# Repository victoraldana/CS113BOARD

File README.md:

# CS113BOARD – Placa de Control

Placa de control diseñada en **KiCad** para el proyecto de *Laboratorio de Electrónica 3* (Universidad, 2026). Usa un módulo **ESP32-S3-DevKitC** como controlador, con una etapa de *latches* (74LS75), un decodificador (74LS138) y *drivers* de potencia (ULN2803A) que se conectan a la carga por conectores JST.

## Contenido del repositorio

| Archivo | Descripción |
|---|---|
| `PLACA DE CONTROL.kicad_pro` | Archivo de proyecto de KiCad |
| `PLACA DE CONTROL.kicad_sch` | Esquemático |
| `PLACA DE CONTROL.kicad_pcb` | Diseño del PCB (espesor 1.6 mm) |
| `PLACA DE CONTROL.kicad_prl` | Preferencias locales del proyecto |
| `PLACA DE CONTROL.png` | Render 3D de la placa |
| `la.pdf` | Documentación de apoyo |
| `LICENSE` | Licencia del proyecto |

## Componentes principales

| Cantidad | Componente | Encapsulado | Función |
|:-:|---|---|---|
| 1 | ESP32-S3-DevKitC | 2 × `PinSocket_1x22_P2.54mm` | Microcontrolador |
| 1 | 74LS138 | DIP-16 | Decodificador 3 a 8 |
| 6 | 74LS75 | DIP-16 | Latches de 4 bits |
| 6 | ULN2803A | DIP-18 | Driver de 8 canales (Darlington) |
| 6 | Conector 1×06 | JST XH B6B-XH-A (2.50 mm) | Conexión a la carga |
| 1 | Conector 1×04 | JST EH B4B-EH-A (2.50 mm) | Conexión auxiliar |

Alimentación: **+5 V** (lógica) y **+12 V** (etapa de potencia), con **GND** común.

## Cómo abrir el proyecto

1. Instala [KiCad](https://www.kicad.org/download/). El proyecto usa el formato de la versión 8 o superior.
2. Clona el repositorio:
   ```bash
   git clone https://github.com/victoraldana/CS113BOARD.git
   ```
3. Abre `PLACA DE CONTROL.kicad_pro`.

## Fabricación

Desde el editor de PCB de KiCad:

1. `Archivo → Fabricación → Archivos Gerber` y `Archivos de taladrado`.
2. Comprueba las reglas con `Inspeccionar → Comprobador de reglas de diseño (DRC)`.
3. Envía los archivos generados al fabricante.

## Licencia

Distribuido bajo la licencia incluida en [LICENSE](LICENSE).

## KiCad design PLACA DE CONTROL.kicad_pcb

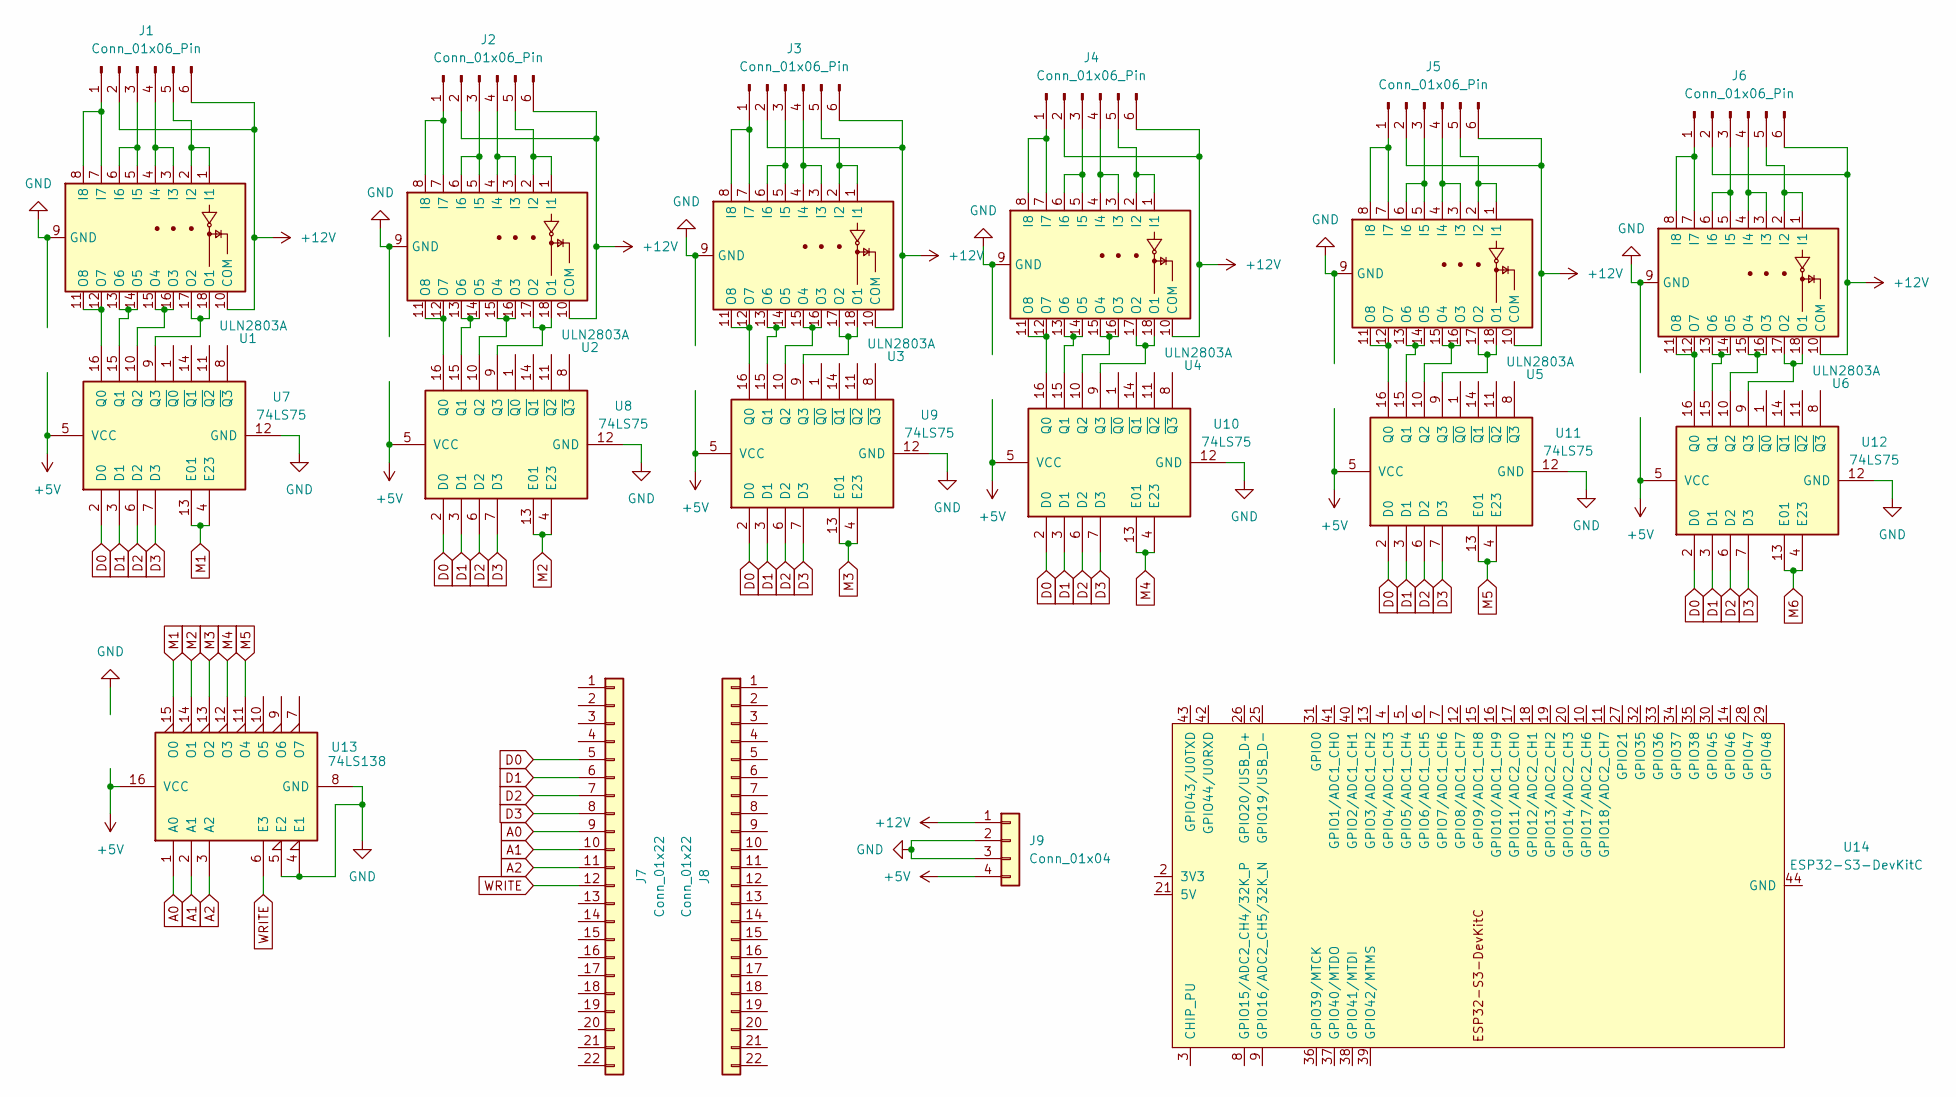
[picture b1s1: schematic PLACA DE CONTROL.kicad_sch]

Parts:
J1, J2, J3, J4, J5, J6: Conn_01x06_Pin; JST_XH_B6B-XH-A_1x06_P2.50mm_Vertical
J7, J8: Conn_01x22; PinSocket_1x22_P2.54mm_Vertical
J9: Conn_01x04; JST_EH_B4B-EH-A_1x04_P2.50mm_Vertical
U1, U2, U3, U4, U5, U6: ULN2803A; DIP-18_W7.62mm_LongPads
U7, U8, U9, U10, U11, U12: 74LS75; DIP-16_W7.62mm
U13: 74LS138; DIP-16_W7.62mm
U14: ESP32-S3-DevKitC

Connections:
+5V: J8.2, J9.4, U7.5 (VCC), U8.5 (VCC), U9.5 (VCC), U10.5 (VCC), U11.5 (VCC), U12.5 (VCC), U13.16 (VCC)
+12V: J1.2, J1.6, J2.2, J2.6, J3.2, J3.6, J4.2, J4.6, J5.2, J5.6, J6.2, J6.6, J9.1, U1.10 (COM), U2.10 (COM), U3.10 (COM), U4.10 (COM), U5.10 (COM), U6.10 (COM)
A0: J7.9, U13.1 (A0)
A1: J7.10, U13.2 (A1)
A2: J7.11, U13.3 (A2)
D0: J7.5, U7.2 (D0), U8.2 (D0), U9.2 (D0), U10.2 (D0), U11.2 (D0), U12.2 (D0)
D1: J7.6, U7.3 (D1), U8.3 (D1), U9.3 (D1), U10.3 (D1), U11.3 (D1), U12.3 (D1)
D2: J7.7, U7.6 (D2), U8.6 (D2), U9.6 (D2), U10.6 (D2), U11.6 (D2), U12.6 (D2)
D3: J7.8, U7.7 (D3), U8.7 (D3), U9.7 (D3), U10.7 (D3), U11.7 (D3), U12.7 (D3)
GND: J8.1, J9.2, J9.3, U1.9 (GND), U2.9 (GND), U3.9 (GND), U4.9 (GND), U5.9 (GND), U6.9 (GND), U7.12 (GND), U8.12 (GND), U9.12 (GND), U10.12 (GND), U11.12 (GND), U12.12 (GND), U13.4 (E1), U13.5 (E2), U13.8 (GND)
M1: U7.4 (E23), U7.13 (E01), U13.15 (O0)
M2: U8.4 (E23), U8.13 (E01), U13.14 (O1)
M3: U9.4 (E23), U9.13 (E01), U13.13 (O2)
M4: U10.4 (E23), U10.13 (E01), U13.12 (O3)
M5: U11.4 (E23), U11.13 (E01), U13.11 (O4)
M6: U12.4 (E23), U12.13 (E01), U13.10 (O5)
unnamed: J1.1, U1.7 (I7), U1.8 (I8)
unnamed: J1.3, U1.5 (I5), U1.6 (I6)
unnamed: J1.4, U1.3 (I3), U1.4 (I4)
unnamed: J1.5, U1.1 (I1), U1.2 (I2)
unnamed: J2.1, U2.7 (I7), U2.8 (I8)
unnamed: J2.3, U2.5 (I5), U2.6 (I6)
unnamed: J2.4, U2.3 (I3), U2.4 (I4)
unnamed: J2.5, U2.1 (I1), U2.2 (I2)
unnamed: J3.1, U3.7 (I7), U3.8 (I8)
unnamed: J3.3, U3.5 (I5), U3.6 (I6)
unnamed: J3.4, U3.3 (I3), U3.4 (I4)
unnamed: J3.5, U3.1 (I1), U3.2 (I2)
unnamed: J4.1, U4.7 (I7), U4.8 (I8)
unnamed: J4.3, U4.5 (I5), U4.6 (I6)
unnamed: J4.4, U4.3 (I3), U4.4 (I4)
unnamed: J4.5, U4.1 (I1), U4.2 (I2)
unnamed: J5.1, U5.7 (I7), U5.8 (I8)
unnamed: J5.3, U5.5 (I5), U5.6 (I6)
unnamed: J5.4, U5.3 (I3), U5.4 (I4)
unnamed: J5.5, U5.1 (I1), U5.2 (I2)
unnamed: J6.1, U6.7 (I7), U6.8 (I8)
unnamed: J6.3, U6.5 (I5), U6.6 (I6)
unnamed: J6.4, U6.3 (I3), U6.4 (I4)
unnamed: J6.5, U6.1 (I1), U6.2 (I2)
unnamed: U1.17 (O2), U1.18 (O1), U7.9 (Q3)
unnamed: U1.15 (O4), U1.16 (O3), U7.10 (Q2)
unnamed: U1.13 (O6), U1.14 (O5), U7.15 (Q1)
unnamed: U1.11 (O8), U1.12 (O7), U7.16 (Q0)
unnamed: U2.17 (O2), U2.18 (O1), U8.9 (Q3)
unnamed: U2.15 (O4), U2.16 (O3), U8.10 (Q2)
unnamed: U2.13 (O6), U2.14 (O5), U8.15 (Q1)
unnamed: U2.11 (O8), U2.12 (O7), U8.16 (Q0)
unnamed: U3.17 (O2), U3.18 (O1), U9.9 (Q3)
unnamed: U3.15 (O4), U3.16 (O3), U9.10 (Q2)
unnamed: U3.13 (O6), U3.14 (O5), U9.15 (Q1)
unnamed: U3.11 (O8), U3.12 (O7), U9.16 (Q0)
unnamed: U4.11 (O8), U4.12 (O7), U10.16 (Q0)
unnamed: U4.13 (O6), U4.14 (O5), U10.15 (Q1)
unnamed: U4.15 (O4), U4.16 (O3), U10.10 (Q2)
unnamed: U4.17 (O2), U4.18 (O1), U10.9 (Q3)
unnamed: U5.11 (O8), U5.12 (O7), U11.16 (Q0)
unnamed: U5.13 (O6), U5.14 (O5), U11.15 (Q1)
unnamed: U5.15 (O4), U5.16 (O3), U11.10 (Q2)
unnamed: U5.17 (O2), U5.18 (O1), U11.9 (Q3)
unnamed: U6.11 (O8), U6.12 (O7), U12.16 (Q0)
unnamed: U6.13 (O6), U6.14 (O5), U12.15 (Q1)
unnamed: U6.15 (O4), U6.16 (O3), U12.10 (Q2)
unnamed: U6.17 (O2), U6.18 (O1), U12.9 (Q3)
unnamed: U14.1 (3V3), U14.2 (3V3)
unnamed: U14.22 (GND), U14.23 (GND), U14.24 (GND), U14.44 (GND)
WRITE: J7.12, U13.6 (E3)

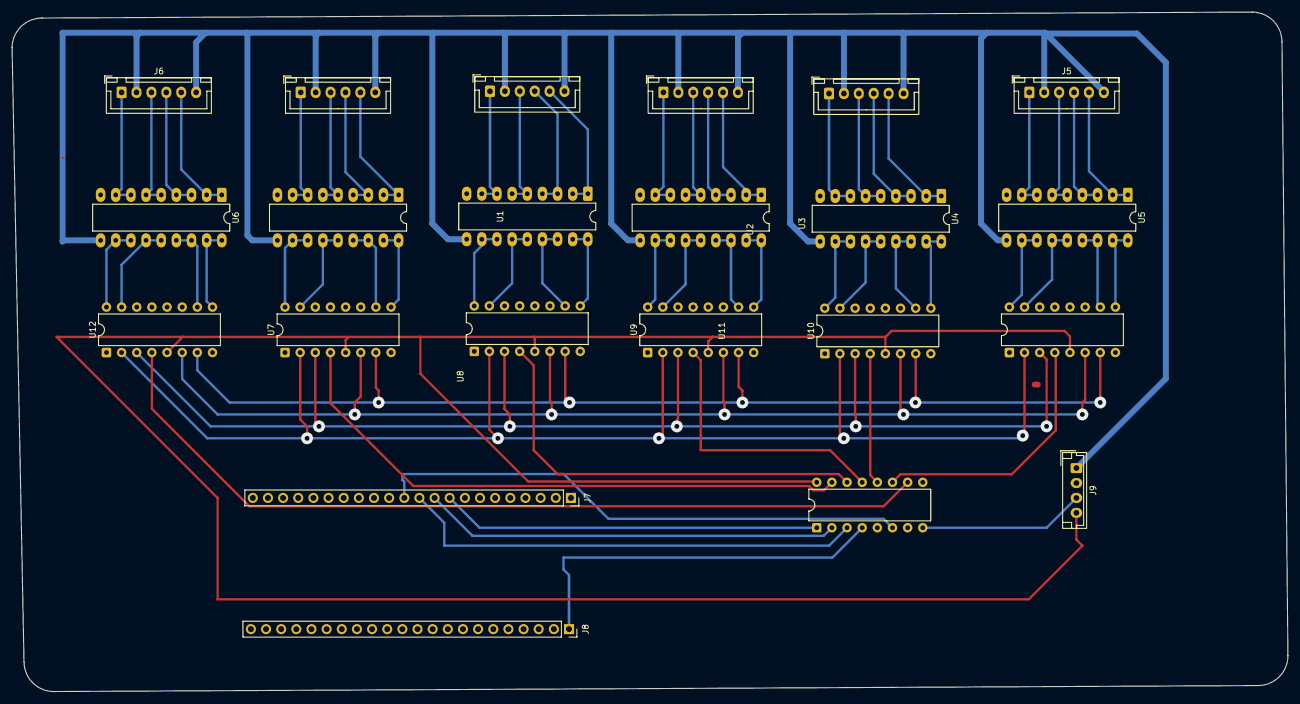
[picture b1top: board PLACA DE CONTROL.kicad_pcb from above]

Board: 2 copper layers, 213.9 x 113.9 mm, 22 parts (0 on the bottom side), 65 nets.
